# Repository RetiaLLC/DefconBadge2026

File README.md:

# DEF CON Badge (2026) — ESP32-S3

Everything you need to hack on the Retia DEF CON badge: hardware docs, pinouts, flashable firmware (including **DOOM**, a full **NES emulator**, **Meshtastic**, **MeshCore**, and **Reticulum**), and example code to get you from "just unboxed" to writing your own firmware.

> **🚀 Start here: the [Badge Launcher v2 "Touch"](https://github.com/RetiaLLC/badge-launcher/releases/tag/v2.0.0)** — the flagship badge experience. One flash + one micro-SD card turns the badge into a pick-what-you-run device: two full-color **touch mesh messengers** (MeshCore + Meshtastic MUI), classic Meshtastic, a **Reticulum RNode**, an **NES emulator** with a 37-game homebrew library, and **WLEDkitty** — switchable from an on-badge menu in ~10 seconds, no computer needed. Comes with a `MESH-101.md` that gets two badges messaging over LoRa in minutes. Flash it from your browser at [scriptkitty.sh](https://scriptkitty.sh). *(Requires a FAT micro-SD card — true of launcher v1 too. Prefer DOOM resident in flash? [Launcher v1 "Classic"](https://github.com/RetiaLLC/badge-launcher/releases/tag/v1.0.0).)*

*Yes, that's DOOM. Flash it in one command — see below.*

## What's on the badge

| | |
|---|---|
| MCU | ESP32-S3-WROOM-1 — dual-core 240 MHz, WiFi + BLE, **8 MB flash**, **2 MB PSRAM**, native USB-C |
| Display | 2.4″ ILI9341 240×320 color TFT + XPT2046 resistive **touch** (MSP2402 module) |
| Radio | RFM95W **LoRa** 915 MHz (SX1276), U.FL antenna |
| Input | 6 face buttons (d-pad + A/B) + BOOT button usable as a 7th |
| Storage | micro-SD slot (tested to 16 GB SDHC) |
| Blinkies | 10× WS2812B NeoPixels, green debug LED |
| Sound | Piezo buzzer (MOSFET-driven) |
| Expansion | SAO v2, QWIIC (I²C), UART header, SPI header, off-board NeoPixel connector |
| Power | 2×AA (boost) or USB-C, auto-switching |

## Quick start: flash DOOM

```bash
pip install esptool
esptool --chip esp32s3 --port <PORT> write-flash 0x0 firmware/doom/doom-audio.factory.bin
```

`<PORT>` is `/dev/cu.usbmodem*` (macOS), `/dev/ttyACM0` (Linux), or `COMx` (Windows). Full instructions, port-finding, and un-bricking: [docs/flashing.md](docs/flashing.md).

## Repo map

```
docs/            pinout.md ← START HERE · hardware.md · flashing.md · sd-card.md
firmware/
  doom/          DOOM shareware, audio + silent builds (flash & play)
  meshtastic/    Meshtastic 2.7.23, standard + low-power builds
  reticulum/     RNode v1.85 — the badge as a Reticulum LoRa transceiver
examples/
  hello-badge/   buttons + LED + buzzer in 100 lines (your first build)
  sd-test/       mount/format/read/write the micro-SD slot
hardware/        KiCad 8 sources + schematic PDF
```

## The three things that bite everyone

1. **The touch controller and the display-module SD slot have crossed data lines** — hardware SPI can't reach them. The main SD slot and everything else work normally. Details: [docs/pinout.md](docs/pinout.md#hardware-quirks).
2. **Native-USB download-mode trap** — DTR-toggling serial monitors + reset = badge stuck "waiting for download". Fix: any esptool command ending in hard-reset. Details: [docs/flashing.md](docs/flashing.md#recovery).
3. **Never TX on LoRa without an antenna.** Receiving is safe; transmitting into nothing can cook the PA.

## Firmware in this repo

- **[DOOM](firmware/doom/)** — the 1993 classic, natively, full speed. D-pad moves, A fires, GPIO0 switches weapons. Audio build plays SFX through the piezo.
- **[Meshtastic](firmware/meshtastic/)** — off-grid LoRa mesh messaging with phone app support; standard, power-optimized, and full **color touch UI (MUI)** builds. **Ready-to-flash touch UI: [meshtastic-mui-v2.7.23 release](https://github.com/RetiaLLC/DefconBadge2026/releases/tag/meshtastic-mui-v2.7.23)** — on-screen keyboard, node map, touch region picker, phone TCP API alongside the home screen.
- **[MeshCore](firmware/meshcore/)** — the badge as a [MeshCore](https://meshcore.io) LoRa mesh node, hardware-verified badge-to-badge (messages + ACKs). The flagship build is a full **standalone touchscreen mesh communicator** — chats, contacts, channels, on-screen keyboard, RF monitor + spectrum analyzer, chimes, D-pad nav — that is simultaneously a BLE companion for the official MeshCore phone app. Plain companion (BLE/USB) builds too. **Ready-to-flash images: [meshcore-v1.0.0 release](https://github.com/RetiaLLC/DefconBadge2026/releases/tag/meshcore-v1.0.0).** Source: **[RetiaLLC/MeshCore](https://github.com/RetiaLLC/MeshCore)** (board variant) + **[RetiaLLC/wadamesh](https://github.com/RetiaLLC/wadamesh)** (touch messenger), both branch `retia-badge`.
- **[Reticulum / RNode](firmware/reticulum/)** — turns the badge into an [RNode](https://unsigned.io/rnode/): a host-controlled 915 MHz LoRa transceiver for the [Reticulum network stack](https://reticulum.network) (NomadNet, Sideband, MeshChat). The default build shows the live RNode status screen (frequency, airtime, channel load, signal) on the TFT. Flash, provision with `rnodeconf`, done — hardware-verified against a Nibble Zero RNode. Full toolkit, source, and Nibble Zero builds live in **[RetiaLLC/NibbleReticulum](https://github.com/RetiaLLC/NibbleReticulum)**.
- **[ESP32 Bus Pirate](firmware/buspirate/)** — a multi-protocol hardware-hacking multitool on the badge TFT (also USB-serial / Wi-Fi web CLI): I²C/SPI/UART/1-Wire/JTAG bus tools with **on-screen bus scan + live register monitor** and a **BME280 dashboard** that colours the ears by temperature, plus a full **on-screen LoRa/RF suite** — heat-map **waterfall**, packet **sniffer**, live **RSSI meter**, band **scanner**, and a **Meshtastic monitor** that decodes real mesh packets on-screen (with a **MeshCore** sniffer preset). Wi-Fi/BLE scanners too. **Start with the [beginner's guide](firmware/buspirate/GUIDE.md).** ⚠ Transmit- & attack-capable (Wi-Fi deauth, BLE spoof, RF jam) — **authorized use only**. Ready-to-flash: **[RetiaLLC/ESP32-Bus-Pirate @ badge-v1.2.1](https://github.com/RetiaLLC/ESP32-Bus-Pirate/releases/tag/badge-v1.2.1)**, ported from [KonradIT/geo-tp](https://github.com/KonradIT/ESP32-Bus-Pirate).
- **[Anemoia NES](https://github.com/RetiaLLC/Anemoia-DefconBadge)** *(standalone repo)* — a full NES emulator: put `.nes` ROMs on the micro-SD card, browse and launch them on the badge, and play with the D-pad + A/B. Save states, chiptune audio through the piezo, and a one-button START/SELECT scheme (tap BOOT = START, hold = pause menu). Ready-to-flash image on the [release page](https://github.com/RetiaLLC/Anemoia-DefconBadge/releases/latest) (also attached to this repo's `anemoia-v1.0.0` release), plus a [curated list of legally-free homebrew games](https://github.com/RetiaLLC/Anemoia-DefconBadge/blob/main/GAMES.md) tested on the badge. Ported from [Shim06/Anemoia-ESP32](https://github.com/Shim06/Anemoia-ESP32).

## Building your own firmware

Both examples are PlatformIO ESP-IDF projects with the badge board definition included — copy one as a template. The short version:

```bash
pip install platformio
cd examples/hello-badge
pio run -t upload --upload-port <PORT>
```

Then open a serial monitor at 115200 and press buttons.

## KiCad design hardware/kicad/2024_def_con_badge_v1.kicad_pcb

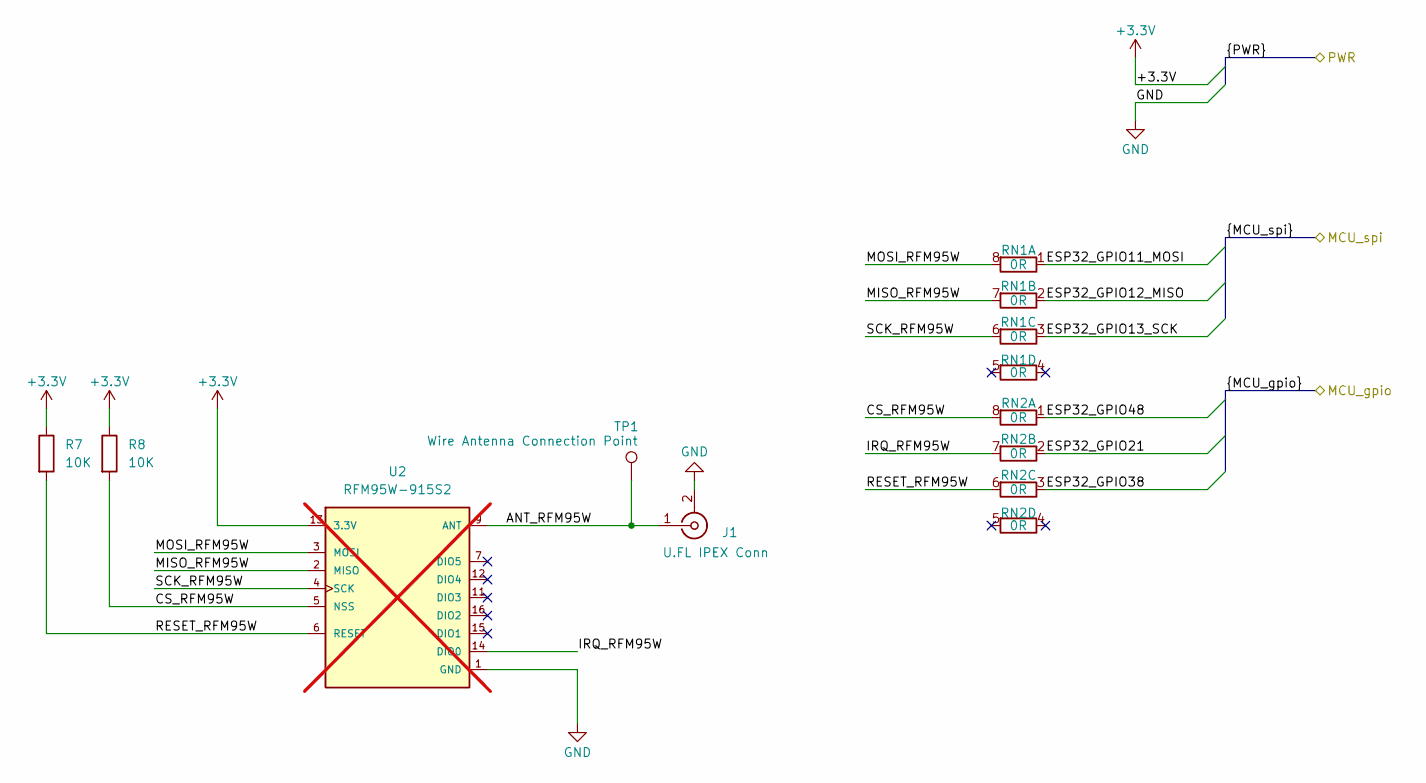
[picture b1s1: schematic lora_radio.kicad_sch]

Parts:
J1: U.FL IPEX Conn; LCSC_U.FL_Hirose_U.FL-R-SMT-1_Vertical; LCSC Part # C5137195
R7, R8: 10K; R_0603_1608Metric_Pad0.98x0.95mm_HandSolder; LCSC Part # C98220
RN1, RN2: 0R; YAGEO_R_ARRAY_4_YC_FAM; LCSC Part # C327053
TP1: Wire Antenna Connection Point; TestPoint_THTPad_D2.0mm_Drill1.0mm
U2: RFM95W-915S2; XCVR_RFM95W-915S2; not fitted

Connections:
+3.3V: R7.1, R8.1, U2.13 (3.3V); also elsewhere on the board
/buttons/ESP32_GPIO21: RN2.2 (R2.1); also elsewhere on the board
/buttons/ESP32_GPIO38: RN2.3 (R3.1); also elsewhere on the board
/buttons/ESP32_GPIO48: RN2.1 (R1.1); also elsewhere on the board
/display/ESP32_GPIO11_MOSI: RN1.1 (R1.1); also elsewhere on the board
/display/ESP32_GPIO12_MISO: RN1.2 (R2.1); also elsewhere on the board
/display/ESP32_GPIO13_SCK: RN1.3 (R3.1); also elsewhere on the board
/lora_radio/ANT_RFM95W: J1.1 (In), TP1.1, U2.9 (ANT)
/lora_radio/CS_RFM95W: R8.2, RN2.8 (R1.2), U2.5 (NSS)
/lora_radio/IRQ_RFM95W: RN2.7 (R2.2), U2.14 (DIO0)
/lora_radio/MISO_RFM95W: RN1.7 (R2.2), U2.2 (MISO)
/lora_radio/MOSI_RFM95W: RN1.8 (R1.2), U2.3 (MOSI)
/lora_radio/RESET_RFM95W: R7.2, RN2.6 (R3.2), U2.6 (RESET)
/lora_radio/SCK_RFM95W: RN1.6 (R3.2), U2.4 (SCK)
GND: J1.2 (Ext), U2.1 (GND), U2.8 (GND), U2.10 (GND); also elsewhere on the board

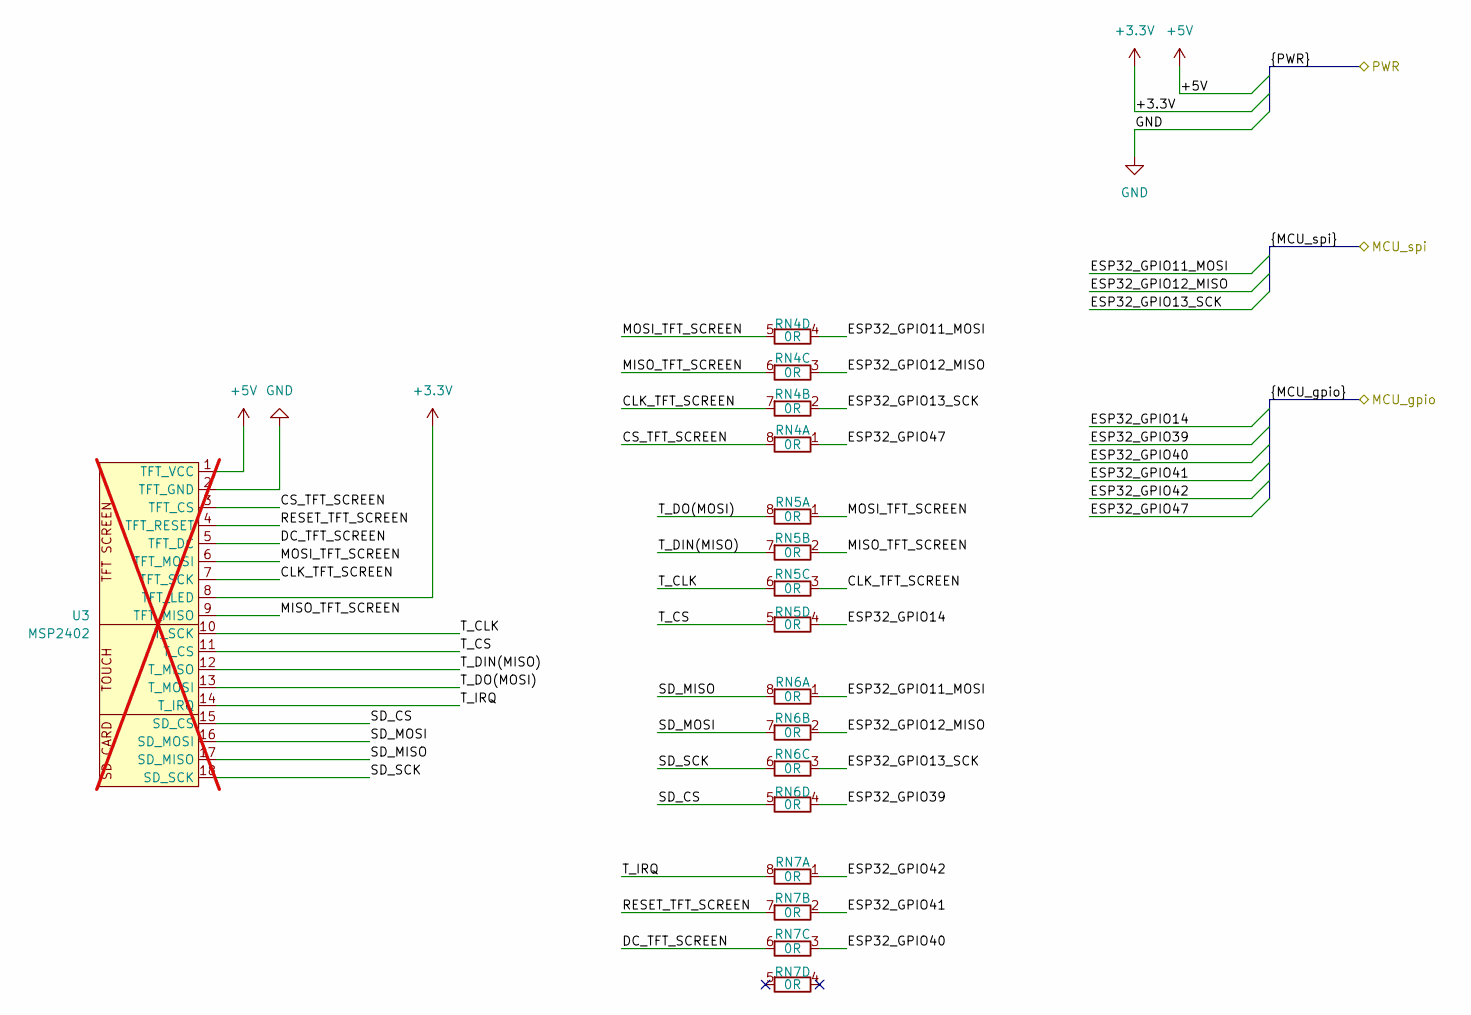
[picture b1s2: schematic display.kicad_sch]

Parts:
RN4, RN5, RN6, RN7: 0R; YAGEO_R_ARRAY_4_YC_FAM; LCSC Part # C327053
U3: MSP2402; LCD_2_4in_PCB_MOUNTED_THRU_HOLE; not fitted

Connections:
+3.3V: U3.8 (TFT_LED); also elsewhere on the board
+5V: U3.1 (TFT_VCC); also elsewhere on the board
/buttons/ESP32_GPIO14: RN5.4 (R4.1); also elsewhere on the board
/buttons/ESP32_GPIO39: RN6.4 (R4.1); also elsewhere on the board
/buttons/ESP32_GPIO40: RN7.3 (R3.1); also elsewhere on the board
/buttons/ESP32_GPIO41: RN7.2 (R2.1); also elsewhere on the board
/buttons/ESP32_GPIO42: RN7.1 (R1.1); also elsewhere on the board
/buttons/ESP32_GPIO47: RN4.1 (R1.1); also elsewhere on the board
/display/CLK_TFT_SCREEN: RN4.7 (R2.2), RN5.3 (R3.1), U3.7 (TFT_SCK)
/display/CS_TFT_SCREEN: RN4.8 (R1.2), U3.3 (TFT_CS)
/display/DC_TFT_SCREEN: RN7.6 (R3.2), U3.5 (TFT_DC)
/display/ESP32_GPIO11_MOSI: RN4.4 (R4.1), RN6.1 (R1.1); also elsewhere on the board
/display/ESP32_GPIO12_MISO: RN4.3 (R3.1), RN6.2 (R2.1); also elsewhere on the board
/display/ESP32_GPIO13_SCK: RN4.2 (R2.1), RN6.3 (R3.1); also elsewhere on the board
/display/MISO_TFT_SCREEN: RN4.6 (R3.2), RN5.2 (R2.1), U3.9 (TFT_MISO)
/display/MOSI_TFT_SCREEN: RN4.5 (R4.2), RN5.1 (R1.1), U3.6 (TFT_MOSI)
/display/RESET_TFT_SCREEN: RN7.7 (R2.2), U3.4 (TFT_RESET)
/display/SD_CS: RN6.5 (R4.2), U3.15 (SD_CS)
/display/SD_MISO: RN6.8 (R1.2), U3.17 (SD_MISO)
/display/SD_MOSI: RN6.7 (R2.2), U3.16 (SD_MOSI)
/display/SD_SCK: RN6.6 (R3.2), U3.18 (SD_SCK)
/display/T_CLK: RN5.6 (R3.2), U3.10 (T_SCK)
/display/T_CS: RN5.5 (R4.2), U3.11 (T_CS)
/display/T_DIN(MISO): RN5.7 (R2.2), U3.12 (T_MISO)
/display/T_DO(MOSI): RN5.8 (R1.2), U3.13 (T_MOSI)
/display/T_IRQ: RN7.8 (R1.2), U3.14 (T_IRQ)
GND: U3.2 (TFT_GND); also elsewhere on the board

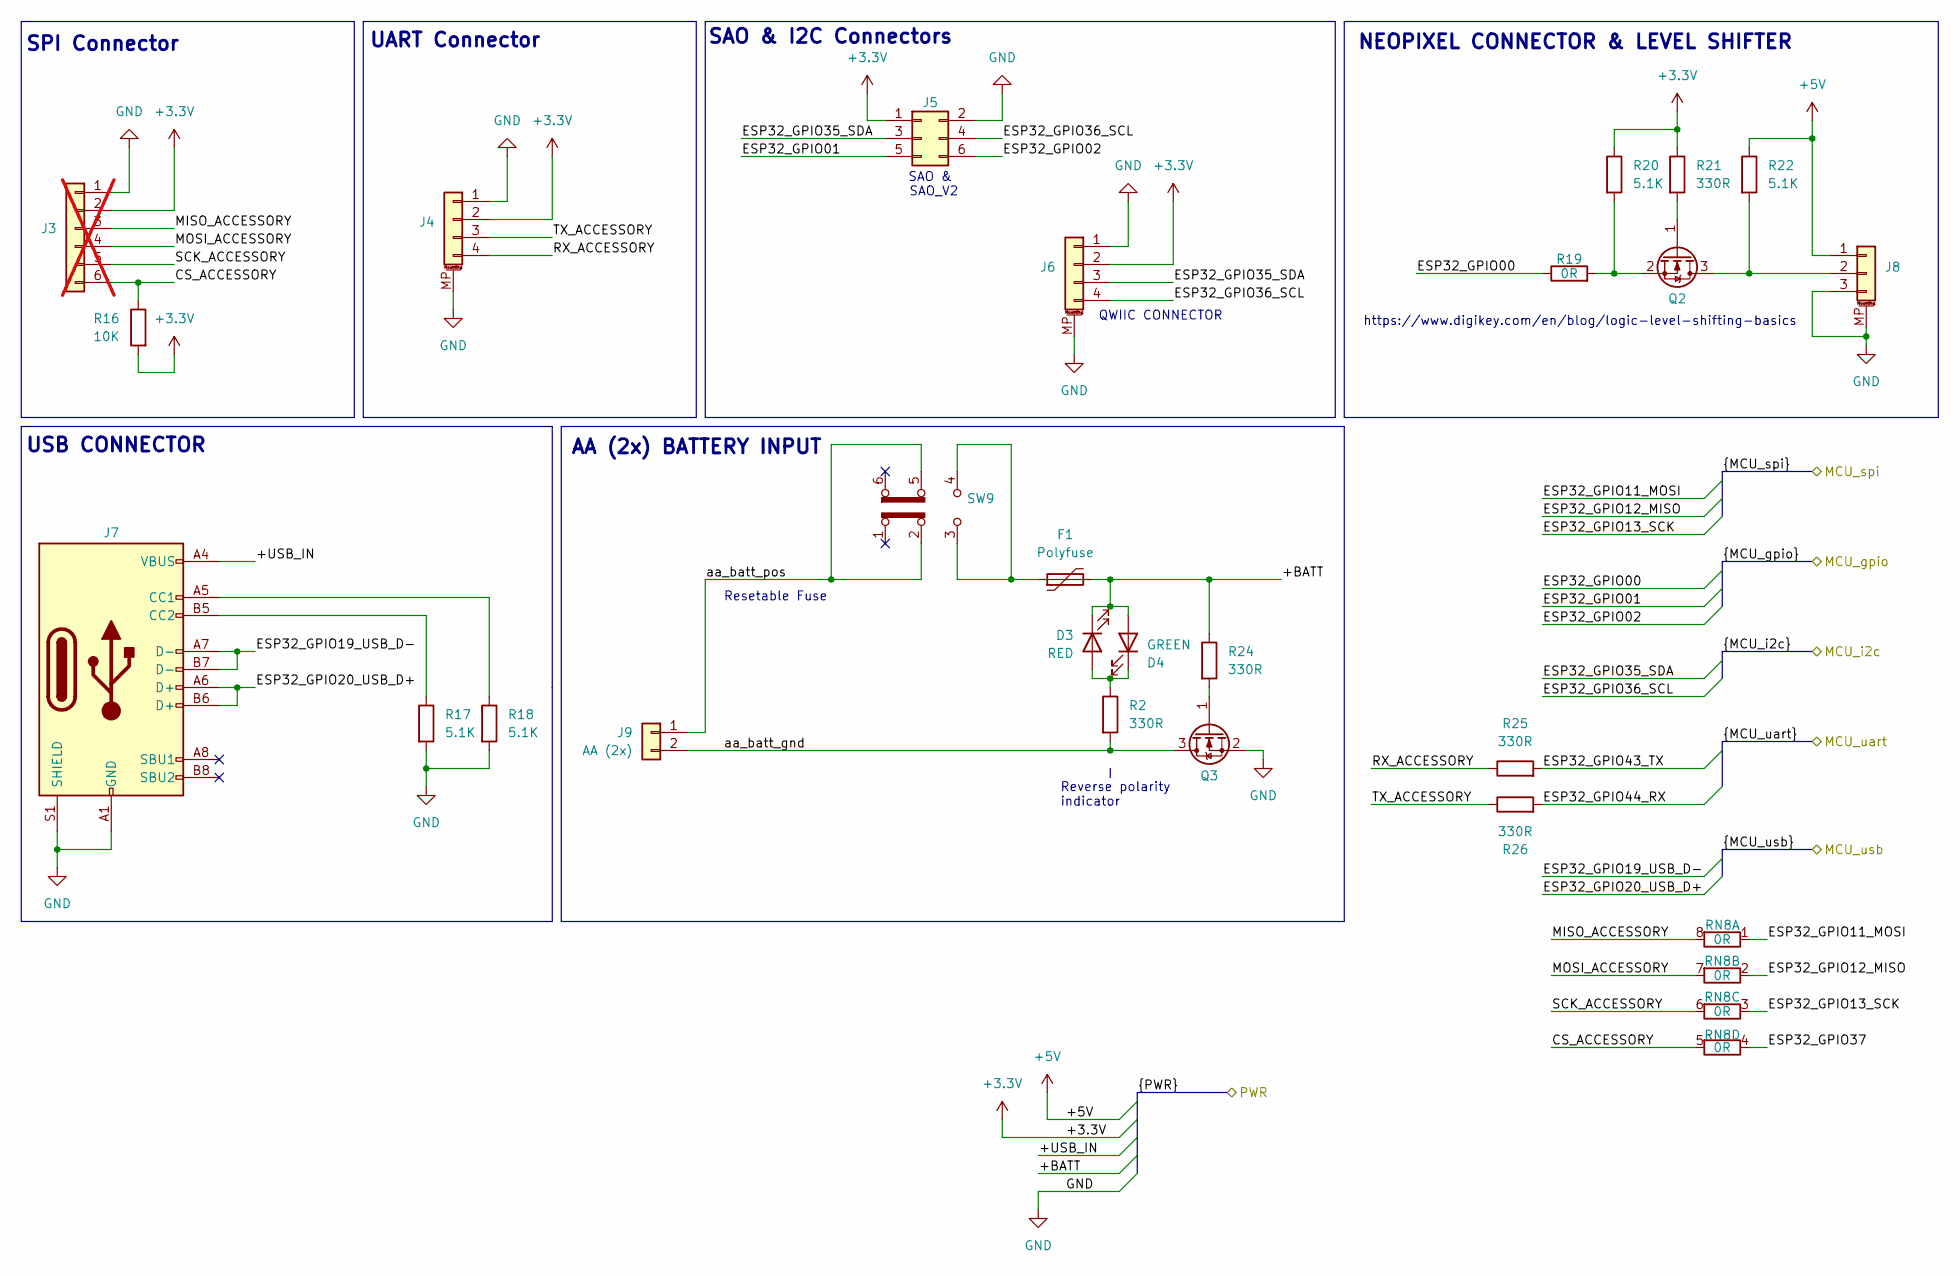
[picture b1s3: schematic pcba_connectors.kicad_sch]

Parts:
D3: RED; LED_0805_2012Metric_Pad1.15x1.40mm_HandSolder; LCSC Part # C94868
D4: GREEN; LED_0805_2012Metric_Pad1.15x1.40mm_HandSolder; LCSC Part # C98221
F1: Polyfuse; Fuse_1206_3216Metric_Pad1.42x1.75mm_HandSolder; LCSC Part # C883133
J3: Conn_01x06; PinHeader_1x06_P2.54mm_Vertical; not fitted
J4, J6: Conn_01x04_MountingPin; QWIIC_CONNECTOR_GENERIC_1x04-1MP_P1.00mm_Horizontal; LCSC Part # C7430446
J5: Conn_02x03_Odd_Even; LCSC_PinSocket_2x03_P2.54mm_Vertical; LCSC Part # C2897404
J7: USB_C_Receptacle_USB2.0_16P; LCSC_USB_C_Receptacle_HCTL_HC-TYPE-C-16P-01A; LCSC Part # C2894897
J8: Conn_01x03_MountingPin; LCSC_JST_PH_S3B-PH-SM4-TB_1x03-1MP_P2.00mm_Horizontal; LCSC Part # C2905020
J9: AA (2x); BatteryHolder_Keystone_2462_2xAA
Q2, Q3: Q_NMOS_GSD; LCSC_SOT-23; LCSC Part # C91714
R2, R21, R24, R25, R26: 330R; R_0603_1608Metric_Pad0.98x0.95mm_HandSolder; LCSC Part # C105881
R16: 10K; R_0603_1608Metric_Pad0.98x0.95mm_HandSolder; LCSC Part # C98220
R17, R18, R20, R22: 5.1K; R_0603_1608Metric_Pad0.98x0.95mm_HandSolder; LCSC Part # C105580
R19: 0R; R_0603_1608Metric_Pad0.98x0.95mm_HandSolder; LCSC Part # C116699
RN8: 0R; YAGEO_R_ARRAY_4_YC_FAM; LCSC Part # C327053
SW9: SW_Slide_DPDT; JLC_K3-2245S-K1; LCSC Part # C223861

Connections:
+3.3V: J3.2, J4.2, J5.1, J6.2, R16.2, R20.1, R21.1; also elsewhere on the board
+5V: J8.1, R22.1; also elsewhere on the board
/buttons/+BATT: D3.1 (K), D4.2 (A), F1.2, R24.1; also elsewhere on the board
/buttons/+USB_IN: J7.A4 (VBUS), J7.A9 (VBUS), J7.B4 (VBUS), J7.B9 (VBUS); also elsewhere on the board
/buttons/ESP32_GPIO00: R19.1; also elsewhere on the board
/buttons/ESP32_GPIO01: J5.5; also elsewhere on the board
/buttons/ESP32_GPIO02: J5.6; also elsewhere on the board
/buttons/ESP32_GPIO37: RN8.4 (R4.1); also elsewhere on the board
/display/ESP32_GPIO11_MOSI: RN8.1 (R1.1); also elsewhere on the board
/display/ESP32_GPIO12_MISO: RN8.2 (R2.1); also elsewhere on the board
/display/ESP32_GPIO13_SCK: RN8.3 (R3.1); also elsewhere on the board
/mcu_block/ESP32_GPIO19_USB_D-: J7.A7 (D-), J7.B7 (D-); also elsewhere on the board
/mcu_block/ESP32_GPIO20_USB_D+: J7.A6 (D+), J7.B6 (D+); also elsewhere on the board
/mcu_block/ESP32_GPIO35_SDA: J5.3, J6.3; also elsewhere on the board
/mcu_block/ESP32_GPIO36_SCL: J5.4, J6.4; also elsewhere on the board
/mcu_block/ESP32_GPIO43_TX: R25.2; also elsewhere on the board
/mcu_block/ESP32_GPIO44_RX: R26.2; also elsewhere on the board
/pcba_connectors/CS_ACCESSORY: J3.6, R16.1, RN8.5 (R4.2)
/pcba_connectors/MISO_ACCESSORY: J3.3, RN8.8 (R1.2)
/pcba_connectors/MOSI_ACCESSORY: J3.4, RN8.7 (R2.2)
/pcba_connectors/RX_ACCESSORY: J4.4, R25.1
/pcba_connectors/SCK_ACCESSORY: J3.5, RN8.6 (R3.2)
/pcba_connectors/TX_ACCESSORY: J4.3, R26.1
/pcba_connectors/aa_batt_gnd: J9.2, Q3.3 (D), R2.2
/pcba_connectors/aa_batt_pos: J9.1, SW9.2 (B), SW9.5 (B)
GND: J3.1, J4.1, J4.MP (MountPin), J5.2, J6.1, J6.MP (MountPin), J7.A1 (GND), J7.A12 (GND), J7.B1 (GND), J7.B12 (GND), J7.S1 (SHIELD), J8.3, J8.MP (MountPin), Q3.2 (S), R17.2, R18.2; also elsewhere on the board
unnamed: D3.2 (A), D4.1 (K), R2.1
unnamed: F1.1, SW9.3 (C), SW9.4 (A)
unnamed: J7.A5 (CC1), R18.1
unnamed: J7.B5 (CC2), R17.1
unnamed: J8.2, Q2.3 (D), R22.2
unnamed: Q2.1 (G), R21.2
unnamed: Q2.2 (S), R19.2, R20.2
unnamed: Q3.1 (G), R24.2

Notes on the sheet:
https://www.digikey.com/en/blog/logic-level-shifting-basics
Reverse polarity indicator
SAO &
QWIIC CONNECTOR
NEOPIXEL CONNECTOR & LEVEL SHIFTER
UART Connector
SAO & I2C Connectors
SAO_V2
Resetable Fuse
USB CONNECTOR
SPI Connector
AA (2x) BATTERY INPUT

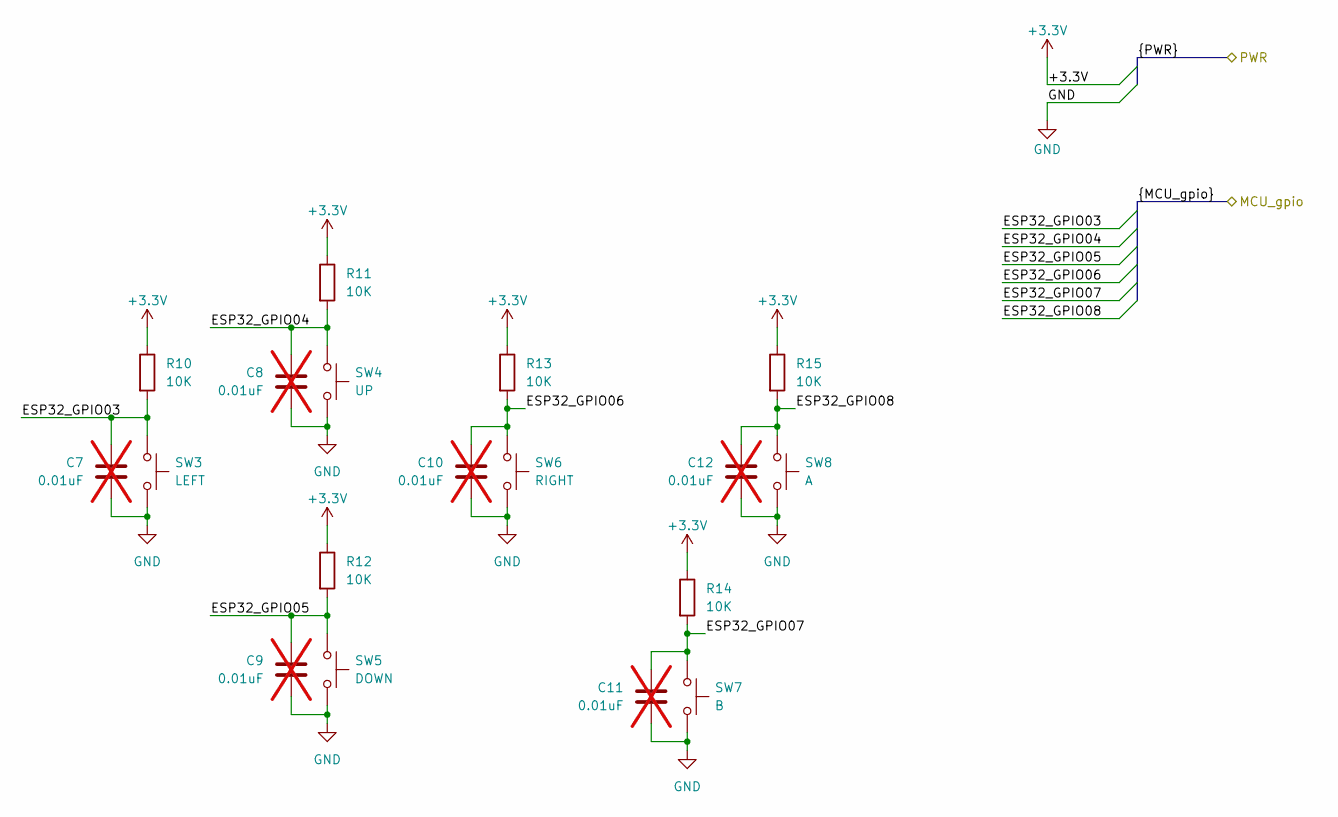
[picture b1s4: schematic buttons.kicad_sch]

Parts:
C7, C8, C9, C10, C11, C12: 0.01uF; C_0603_1608Metric_Pad1.08x0.95mm_HandSolder; LCSC Part # C92490; not fitted
R10, R11, R12, R13, R14, R15: 10K; R_0603_1608Metric_Pad0.98x0.95mm_HandSolder; LCSC Part # C98220
SW3: LEFT; JLC_TS-1080W-A7B3-D1; LCSC Part # C499306
SW4: UP; JLC_TS-1080W-A7B3-D1; LCSC Part # C499306
SW5: DOWN; JLC_TS-1080W-A7B3-D1; LCSC Part # C499306
SW6: RIGHT; JLC_TS-1080W-A7B3-D1; LCSC Part # C499306
SW7: B; JLC_TS-1080W-A7B3-D1; LCSC Part # C499306
SW8: A; JLC_TS-1080W-A7B3-D1; LCSC Part # C499306

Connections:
+3.3V: R10.1, R11.1, R12.1, R13.1, R14.1, R15.1; also elsewhere on the board
/buttons/ESP32_GPIO03: C7.1, R10.2, SW3.1; also elsewhere on the board
/buttons/ESP32_GPIO04: C8.1, R11.2, SW4.1; also elsewhere on the board
/buttons/ESP32_GPIO05: C9.1, R12.2, SW5.1; also elsewhere on the board
/buttons/ESP32_GPIO06: C10.1, R13.2, SW6.1; also elsewhere on the board
/buttons/ESP32_GPIO07: C11.1, R14.2, SW7.1; also elsewhere on the board
/buttons/ESP32_GPIO08: C12.1, R15.2, SW8.1; also elsewhere on the board
GND: C7.2, C8.2, C9.2, C10.2, C11.2, C12.2, SW3.2, SW4.2, SW5.2, SW6.2, SW7.2, SW8.2; also elsewhere on the board

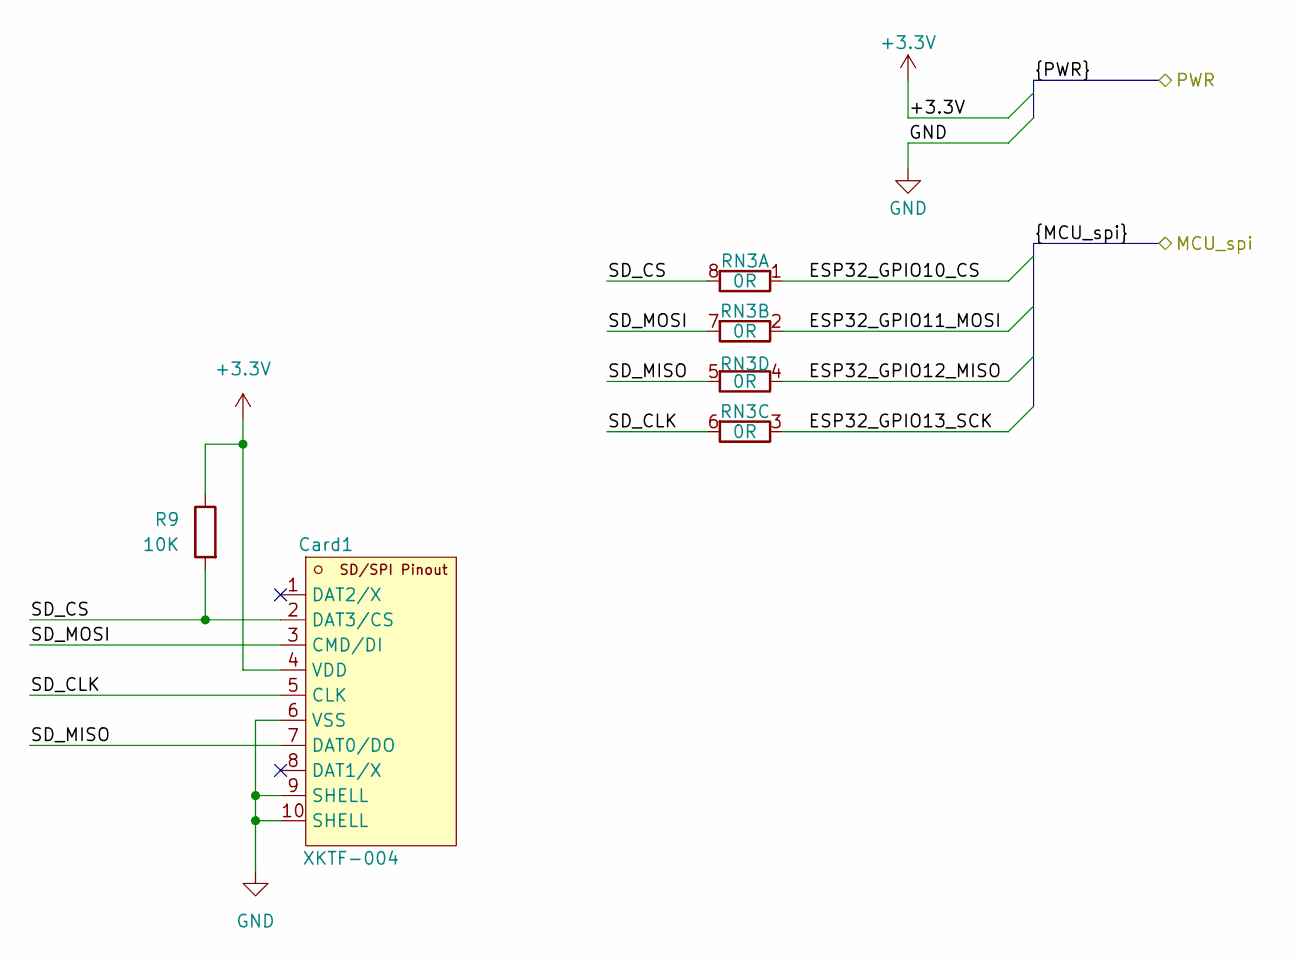
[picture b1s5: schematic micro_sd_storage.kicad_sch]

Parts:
Card1: XKTF-004; xkb_connection_XKTF-004; LCSC Part # C266612
R9: 10K; R_0603_1608Metric_Pad0.98x0.95mm_HandSolder; LCSC Part # C98220
RN3: 0R; YAGEO_R_ARRAY_4_YC_FAM; LCSC Part # C327053

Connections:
+3.3V: Card1.4 (VDD), R9.1; also elsewhere on the board
/display/ESP32_GPIO10_CS: RN3.1 (R1.1); also elsewhere on the board
/display/ESP32_GPIO11_MOSI: RN3.2 (R2.1); also elsewhere on the board
/display/ESP32_GPIO12_MISO: RN3.4 (R4.1); also elsewhere on the board
/display/ESP32_GPIO13_SCK: RN3.3 (R3.1); also elsewhere on the board
/micro_sd_storage/SD_CLK: Card1.5 (CLK), RN3.6 (R3.2)
/micro_sd_storage/SD_CS: Card1.2 (DAT3/CS), R9.2, RN3.8 (R1.2)
/micro_sd_storage/SD_MISO: Card1.7 (DAT0/DO), RN3.5 (R4.2)
/micro_sd_storage/SD_MOSI: Card1.3 (CMD/DI), RN3.7 (R2.2)
GND: Card1.6 (VSS), Card1.9 (SHELL), Card1.10 (SHELL); also elsewhere on the board

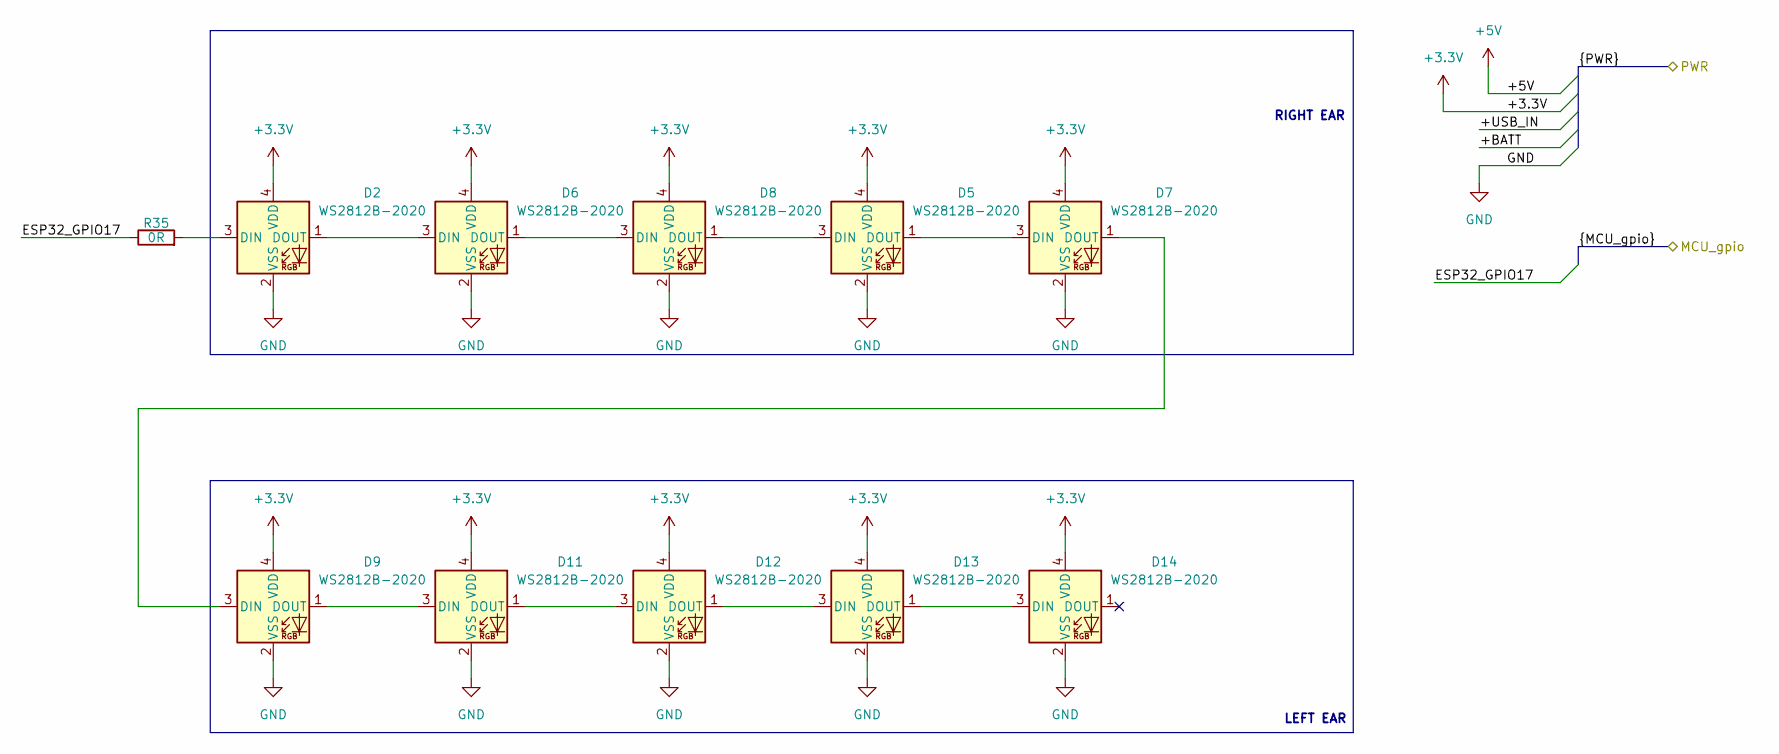
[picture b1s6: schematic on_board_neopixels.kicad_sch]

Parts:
D2, D5, D6, D7, D8, D9, D11, D12, D13, D14: WS2812B-2020; LED_WS2812B-2020_PLCC4_2.0x2.0mm; LCSC Part # C965555
R35: 0R; R_0603_1608Metric_Pad0.98x0.95mm_HandSolder; LCSC Part # C116699

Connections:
+3.3V: D2.4 (VDD), D5.4 (VDD), D6.4 (VDD), D7.4 (VDD), D8.4 (VDD), D9.4 (VDD), D11.4 (VDD), D12.4 (VDD), D13.4 (VDD), D14.4 (VDD); also elsewhere on the board
/buttons/ESP32_GPIO17: R35.1; also elsewhere on the board
GND: D2.2 (VSS), D5.2 (VSS), D6.2 (VSS), D7.2 (VSS), D8.2 (VSS), D9.2 (VSS), D11.2 (VSS), D12.2 (VSS), D13.2 (VSS), D14.2 (VSS); also elsewhere on the board
unnamed: D2.3 (DIN), R35.2
unnamed: D2.1 (DOUT), D6.3 (DIN)
unnamed: D5.3 (DIN), D8.1 (DOUT)
unnamed: D5.1 (DOUT), D7.3 (DIN)
unnamed: D6.1 (DOUT), D8.3 (DIN)
unnamed: D7.1 (DOUT), D9.3 (DIN)
unnamed: D9.1 (DOUT), D11.3 (DIN)
unnamed: D11.1 (DOUT), D12.3 (DIN)
unnamed: D12.1 (DOUT), D13.3 (DIN)
unnamed: D13.1 (DOUT), D14.3 (DIN)

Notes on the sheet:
RIGHT EAR
LEFT EAR

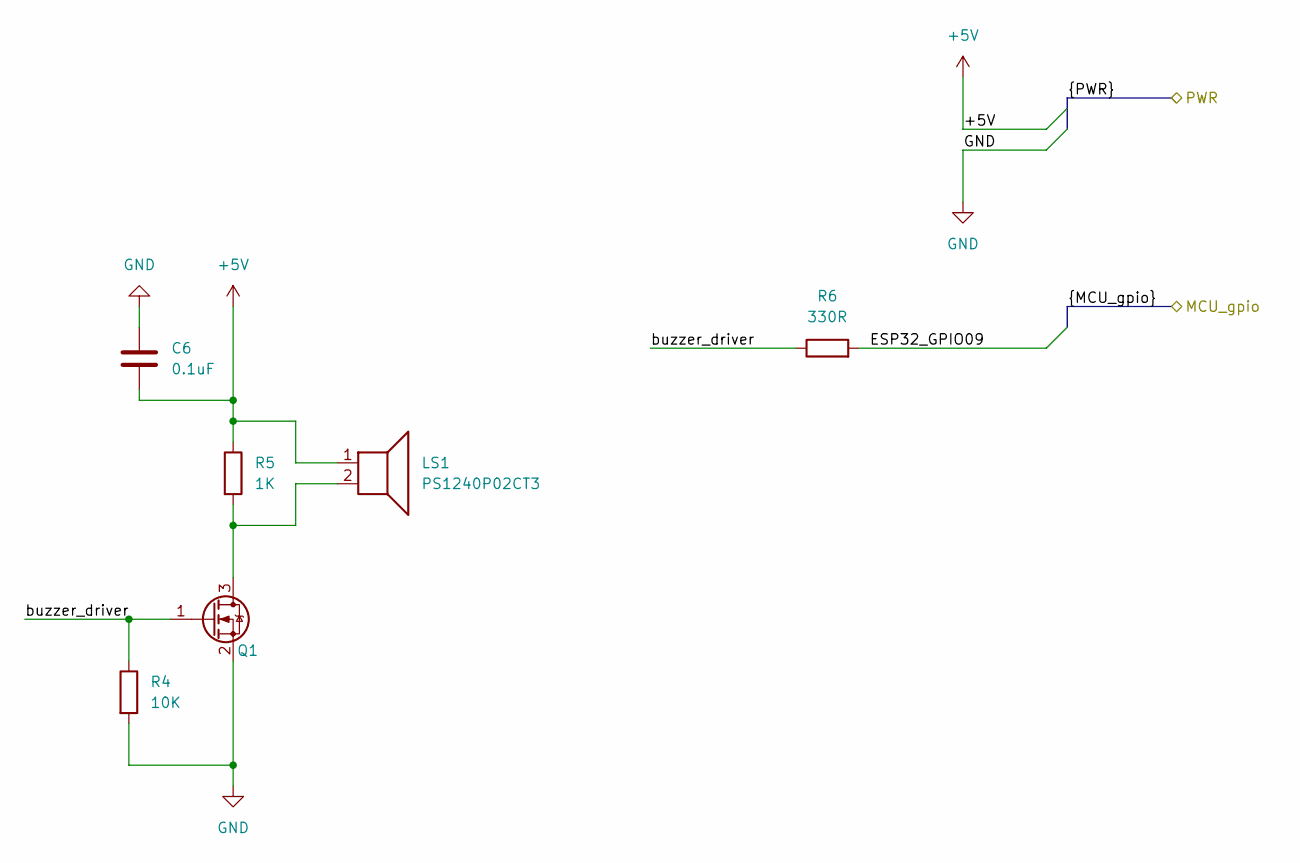
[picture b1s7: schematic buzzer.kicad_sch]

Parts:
C6: 0.1uF; C_0603_1608Metric_Pad1.08x0.95mm_HandSolder; LCSC Part # C92490
LS1: PS1240P02CT3; tdk_PS1240P02CT3_buzzer; LCSC Part # C76873
Q1: Q_NMOS_GSD; LCSC_SOT-23; LCSC Part # C91714
R4: 10K; R_0603_1608Metric_Pad0.98x0.95mm_HandSolder; LCSC Part # C98220
R5: 1K; R_0603_1608Metric_Pad0.98x0.95mm_HandSolder; LCSC Part # C22548
R6: 330R; R_0603_1608Metric_Pad0.98x0.95mm_HandSolder; LCSC Part # C105881

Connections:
+5V: C6.2, LS1.1, R5.1; also elsewhere on the board
/buttons/ESP32_GPIO09: R6.2; also elsewhere on the board
/buzzer/buzzer_driver: Q1.1 (G), R4.1, R6.1
GND: C6.1, Q1.2 (S), R4.2; also elsewhere on the board
unnamed: LS1.2, Q1.3 (D), R5.2

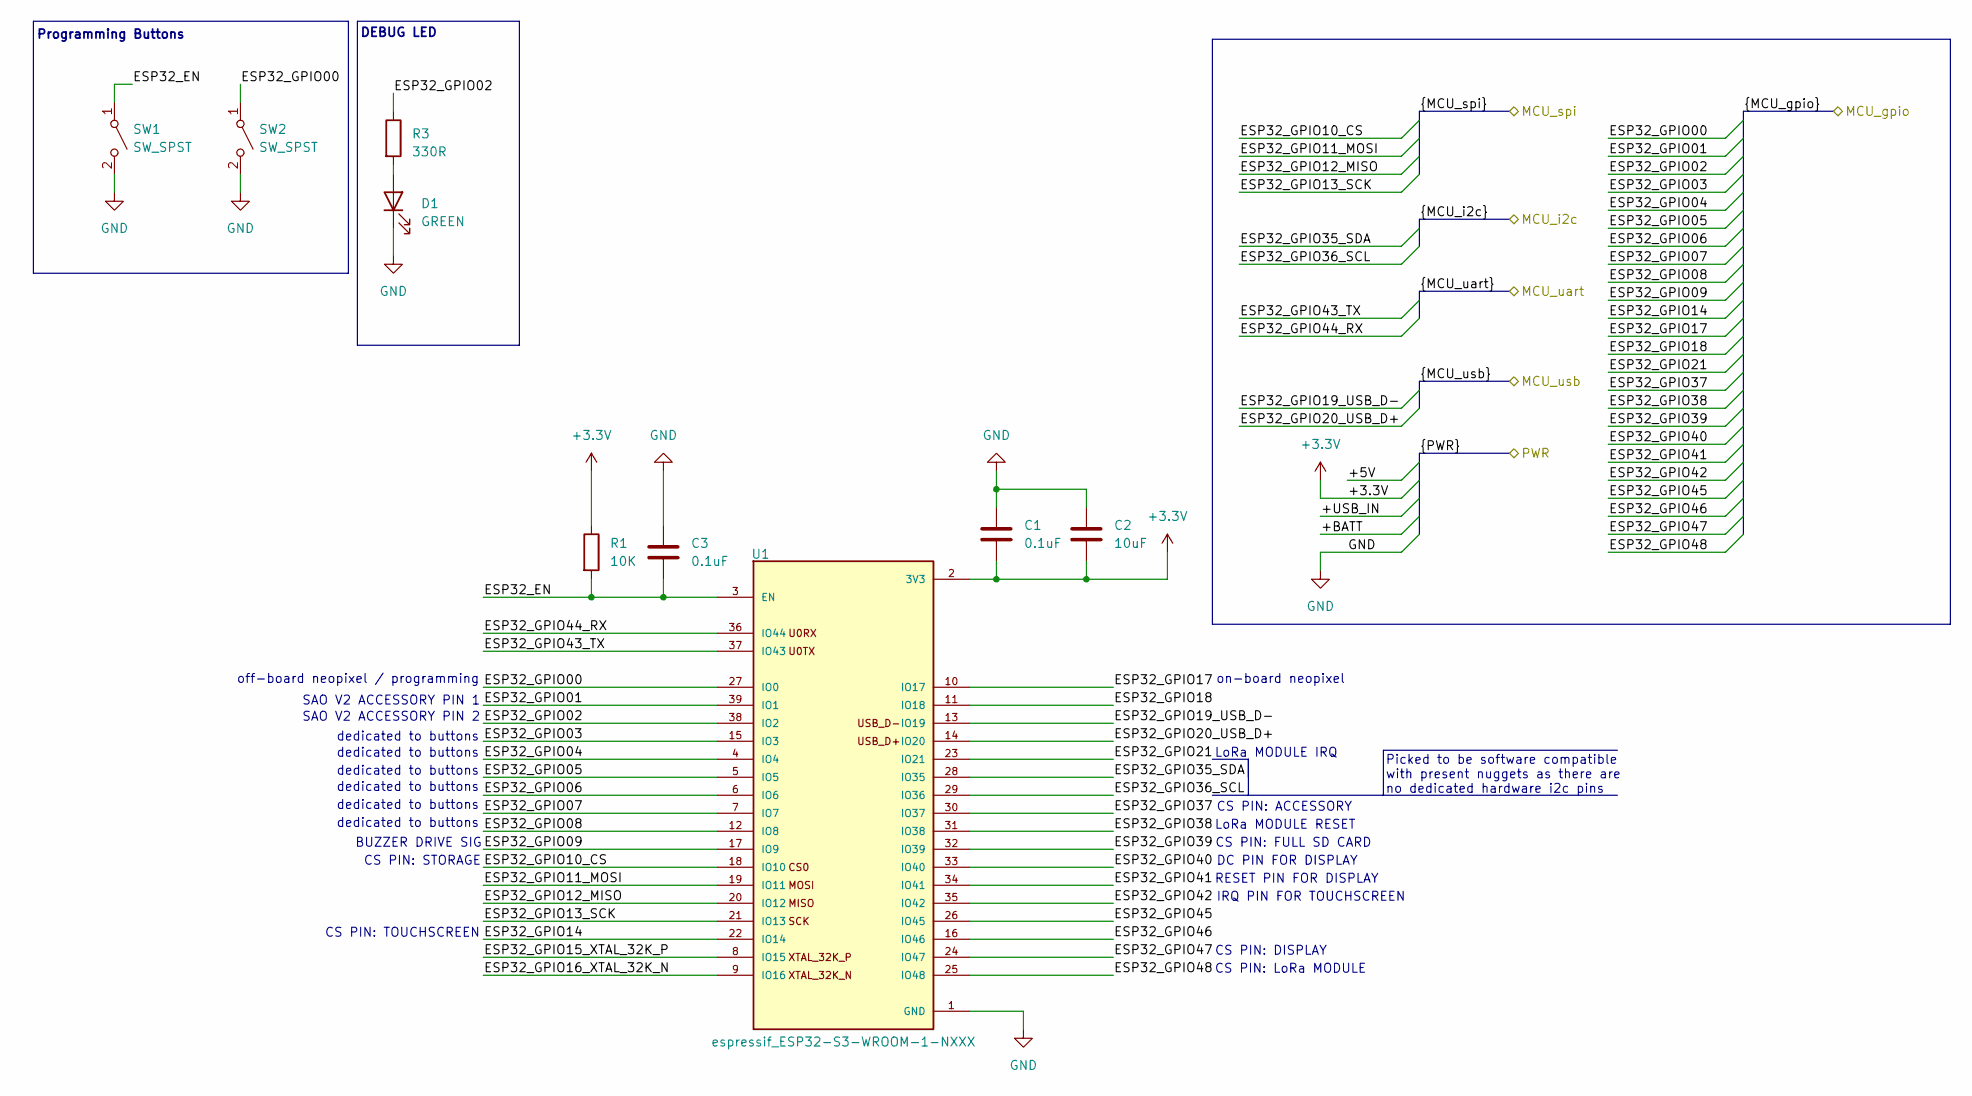
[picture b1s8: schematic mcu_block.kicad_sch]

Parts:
C1, C3: 0.1uF; C_0603_1608Metric_Pad1.08x0.95mm_HandSolder; LCSC Part # C92490
C2: 10uF; C_0603_1608Metric_Pad1.08x0.95mm_HandSolder; LCSC Part # C326057
D1: GREEN; LED_0805_2012Metric_Pad1.15x1.40mm_HandSolder; LCSC Part # C98221
R1: 10K; R_0603_1608Metric_Pad0.98x0.95mm_HandSolder; LCSC Part # C98220
R3: 330R; R_0603_1608Metric_Pad0.98x0.95mm_HandSolder; LCSC Part # C105881
SW1, SW2: SW_SPST; SW_SPST_PTS641T; LCSC Part # C285456
U1: espressif_ESP32-S3-WROOM-1-NXXX; XCVR_ESP32-S3-WROOM-1; LCSC Part # C2913204

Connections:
+3.3V: C1.2, C2.2, R1.1, U1.2 (3V3); also elsewhere on the board
/buttons/ESP32_GPIO00: SW2.1 (A), U1.27 (IO0); also elsewhere on the board
/buttons/ESP32_GPIO01: U1.39 (IO1); also elsewhere on the board
/buttons/ESP32_GPIO02: R3.1, U1.38 (IO2); also elsewhere on the board
/buttons/ESP32_GPIO03: U1.15 (IO3); also elsewhere on the board
/buttons/ESP32_GPIO04: U1.4 (IO4); also elsewhere on the board
/buttons/ESP32_GPIO05: U1.5 (IO5); also elsewhere on the board
/buttons/ESP32_GPIO06: U1.6 (IO6); also elsewhere on the board
/buttons/ESP32_GPIO07: U1.7 (IO7); also elsewhere on the board
/buttons/ESP32_GPIO08: U1.12 (IO8); also elsewhere on the board
/buttons/ESP32_GPIO09: U1.17 (IO9); also elsewhere on the board
/buttons/ESP32_GPIO14: U1.22 (IO14); also elsewhere on the board
/buttons/ESP32_GPIO17: U1.10 (IO17); also elsewhere on the board
/buttons/ESP32_GPIO18: U1.11 (IO18)
/buttons/ESP32_GPIO21: U1.23 (IO21); also elsewhere on the board
/buttons/ESP32_GPIO37: U1.30 (IO37); also elsewhere on the board
/buttons/ESP32_GPIO38: U1.31 (IO38); also elsewhere on the board
/buttons/ESP32_GPIO39: U1.32 (IO39); also elsewhere on the board
/buttons/ESP32_GPIO40: U1.33 (IO40); also elsewhere on the board
/buttons/ESP32_GPIO41: U1.34 (IO41); also elsewhere on the board
/buttons/ESP32_GPIO42: U1.35 (IO42); also elsewhere on the board
/buttons/ESP32_GPIO45: U1.26 (IO45)
/buttons/ESP32_GPIO46: U1.16 (IO46)
/buttons/ESP32_GPIO47: U1.24 (IO47); also elsewhere on the board
/buttons/ESP32_GPIO48: U1.25 (IO48); also elsewhere on the board
/display/ESP32_GPIO10_CS: U1.18 (IO10); also elsewhere on the board
/display/ESP32_GPIO11_MOSI: U1.19 (IO11); also elsewhere on the board
/display/ESP32_GPIO12_MISO: U1.20 (IO12); also elsewhere on the board
/display/ESP32_GPIO13_SCK: U1.21 (IO13); also elsewhere on the board
/mcu_block/ESP32_EN: C3.2, R1.2, SW1.1 (A), U1.3 (EN)
/mcu_block/ESP32_GPIO15_XTAL_32K_P: U1.8 (IO15)
/mcu_block/ESP32_GPIO16_XTAL_32K_N: U1.9 (IO16)
/mcu_block/ESP32_GPIO19_USB_D-: U1.13 (IO19); also elsewhere on the board
/mcu_block/ESP32_GPIO20_USB_D+: U1.14 (IO20); also elsewhere on the board
/mcu_block/ESP32_GPIO35_SDA: U1.28 (IO35); also elsewhere on the board
/mcu_block/ESP32_GPIO36_SCL: U1.29 (IO36); also elsewhere on the board
/mcu_block/ESP32_GPIO43_TX: U1.37 (IO43); also elsewhere on the board
/mcu_block/ESP32_GPIO44_RX: U1.36 (IO44); also elsewhere on the board
GND: C1.1, C2.1, C3.1, D1.1 (K), SW1.2 (B), SW2.2 (B), U1.1 (GND), U1.40 (GND), U1.41_1 (GND), U1.41_2 (GND), U1.41_3 (GND), U1.41_4 (GND), U1.41_5 (GND), U1.41_6 (GND), U1.41_7 (GND), U1.41_8 (GND), U1.41_9 (GND), U1.41_10 (GND), U1.41_11 (GND), U1.41_12 (GND), U1.41_13 (GND), U1.41_14 (GND), U1.41_15 (GND), U1.41_16 (GND), U1.41_17 (GND); also elsewhere on the board
unnamed: D1.2 (A), R3.2

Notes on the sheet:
BUZZER DRIVE SIG
dedicated to buttons
CS PIN: ACCESSORY
RESET PIN FOR DISPLAY
CS PIN: TOUCHSCREEN
SAO V2 ACCESSORY PIN 2
DC PIN FOR DISPLAY
CS PIN: FULL SD CARD
Programming Buttons
LoRa MODULE IRQ
CS PIN: DISPLAY
IRQ PIN FOR TOUCHSCREEN
CS PIN: LoRa MODULE
DEBUG LED
LoRa MODULE RESET
CS PIN: STORAGE
Picked to be software compatible with present nuggets as there are no dedicated hardware i2c pins
on-board neopixel
SAO V2 ACCESSORY PIN 1
off-board neopixel / programming
